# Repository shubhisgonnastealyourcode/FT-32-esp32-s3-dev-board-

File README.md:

# FT-32-ESP32S3--Dev-Board-
Custom ESP32-S3 Development Board with Header Pins for Display and RGB LED

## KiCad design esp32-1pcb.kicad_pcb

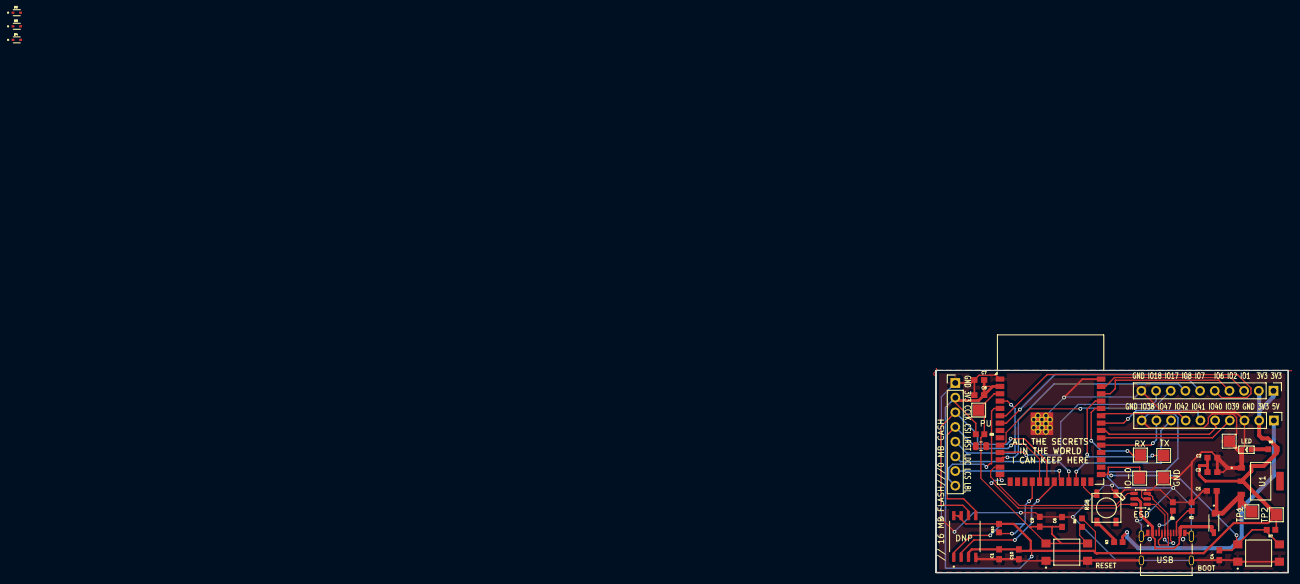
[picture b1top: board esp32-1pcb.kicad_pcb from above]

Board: 2 copper layers, 61.0 x 35.0 mm, 42 parts (0 on the bottom side), 38 nets.

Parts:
BOOT: TL3305AF260QG; SW_TL3305AF260QG
C1: 10uF; CAPC1608X90
C2, C4, C6, C7, C10: 0u1F; CAPC1608X90
C3, C5, C8: 10uf; CAPC1608X90
C9: 1uf; CAPC1608X90
D1: 1N5819HW-7-F; SOD3715X145N
D2, D3, D4: LESD5D5.0CT1G; TVS_LESD5D5.0CT1G
DNP: W25Q128JVSIQ; SOIC127P790X216-8N
ESD: USBLC6-2SC6; SOT-23-6
GND: GND; TestPoint_Pad_2.0x2.0mm
IO-0: IO; TestPoint_Pad_2.0x2.0mm
J2: LCD; PinHeader_1x08_P2.54mm_Vertical
J5: header2; PinHeader_1x10_P2.54mm_Vertical
J6: header1; PinHeader_1x10_P2.54mm_Vertical
LED: LED-SMD-RED-DIFFUSED_0603_; LED-0603
PU: EN; TestPoint_Pad_2.0x2.0mm
R1, R2, R6, R9: 5k1; RESC1607X60N
R3, R7, R8, R10: 10k; RESC1607X60N
RESET: TL3305AF260QG; SW_TL3305AF260QG
RGB: WS2812B
RX: RX; TestPoint_Pad_2.0x2.0mm
TP1: 5V; TestPoint_Pad_2.0x2.0mm
TP2: 3V; TestPoint_Pad_2.0x2.0mm
TP8: GND; TestPoint_Pad_2.0x2.0mm
TX: TX; TestPoint_Pad_2.0x2.0mm
U1: AMS1117-3.3; SOT229P700X180-4N
U5: ESP32-S3-WROOM-1
USB: TYPE-C-31-M-12; HRO_TYPE-C-31-M-12

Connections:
CHIP_PU: C6.2, C9.2, PU.1, R8.2, R9.2, RESET.3, RESET.4, U5.3 (EN)
COM_CLK: DNP.6 (CLK), J2.3, U5.20 (IO12)
COM_MOSI: DNP.5 (DI(IO0)), J2.4, U5.19 (IO11)
D+: ESD.6 (I/O1), U5.14 (USB_D+)
D-: ESD.4 (I/O2), U5.13 (USB_D-)
ESP_3V3: C1.2, C2.2, C3.2, C7.2, C8.2, C10.2, DNP.3 (/WP(IO2)), DNP.7 (/HOLD/RESET(IO3)), DNP.8 (VCC), J2.2, J5.1, J5.2, J6.2, R6.1, R7.1, R8.1, R9.1, R10.2, TP2.1, U1.2 (VOUT), U5.2 (3V3)
GND: BOOT.1, BOOT.2, C1.1, C2.1, C3.1, C4.1, C5.1, C6.1, C7.1, C8.1, C9.1, C10.1, DNP.4 (GND), ESD.2 (GND), GND.1, J2.1, J5.10, J6.3, J6.10, LED.-, R1.1, R2.1, RESET.1, RESET.2, RGB.3-GND (GND), TP8.1, U1.1 (GND/ADJ), U5.1 (GND), U5.40 (GND), U5.41 (GND), USB.A1_B12 (GND), USB.B1_A12 (GND), USB.S1 (SHIELD), USB.S2 (SHIELD), USB.S3 (SHIELD), USB.S4 (SHIELD)
GPIO0: BOOT.3, BOOT.4, C4.2, IO-0.1, R7.2, U5.27 (IO0)
IO1: J5.3, U5.39 (IO1)
IO2: J5.4, U5.38 (IO2)
IO6: J5.5, U5.6 (IO6)
IO7: J5.6, U5.7 (IO7)
IO8: J5.7, U5.12 (IO8)
IO17: J5.8, U5.10 (IO17)
IO18: J5.9, U5.11 (IO18)
IO38: J6.9, U5.31 (IO38)
IO39: J6.4, U5.32 (IO39)
IO40: J6.5, U5.33 (IO40)
IO41: J6.6, U5.34 (IO41)
IO42: J6.7, U5.35 (IO42)
IO47: J6.8, U5.24 (IO47)
LCD_BL: J2.8, U5.5 (IO5)
LCD_CS: J2.7, U5.22 (IO14)
LCD_DC: J2.6, U5.23 (IO21)
LCD_RST: J2.5, U5.4 (IO4)
MEM_CS: DNP.1 (/CS), R10.1, U5.18 (IO10)
MEM_MISO: DNP.2 (DO(IO1)), U5.21 (IO13)
unnamed: LED.+, R6.2
unnamed: R1.2, USB.A5 (CC1)
unnamed: R2.2, USB.B5 (CC2)
unnamed: ESD.3 (I/O2), USB.A7 (DN1), USB.B7 (DN2)
unnamed: ESD.1 (I/O1), USB.A6 (DP1), USB.B6 (DP2)
unnamed: R3.1, RGB.1-VDD (VDD)
unnamed: RX.1, U5.36 (RXD0)
unnamed: TX.1, U5.37 (TXD0)
RGB: RGB.4-DIN (DI), U5.25 (IO48)
VBUS: D1.A, ESD.5 (VBUS), USB.A4_B9 (VBUS), USB.B4_A9 (VBUS)
VCC_5V: C5.2, D1.C, J6.1, R3.2, TP1.1, U1.3 (VIN)
